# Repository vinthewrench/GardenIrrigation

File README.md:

# GardenIrrigation

This is the hardware for Farm automation made easy as Pi

The entire series is at https://www.vinthewrench.com/p/off-grid-farm-automation-raspberry-pi

Garden Irrigation Board

<object data="Garden PCB schematic.pdf" type="application/pdf" width="600px" height="500px">
    <embed src="Garden PCB schematic.pdf">
        <p>This browser does not support PDFs. Please download the PDF to view it: <a href="Garden PCB schematic.pdf">Download PDF</a>.</p>
    </embed>
</object>

DRV103 Plugin Board

<object data="DRV103 Solenoid Driver Board.pdf" type="application/pdf" width="600px" height="500px">
    <embed src="DRV103 Solenoid Driver Board.pdf">
        <p>This browser does not support PDFs. Please download the PDF to view it: <a href="DRV103 Solenoid Driver Board.pdf">Download PDF</a>.</p>
    </embed>
</object>

# Articles

* [Farm automation made easy as Pi](https://www.vinthewrench.com/p/raspberry-pi-internet-of-things-part)
* [Controlling the Irrigation valves.](https://www.vinthewrench.com/p/raspberry-pi-internet-of-things-part-23c)
* [Reading the Temperature with 1-wire Sensors](https://www.vinthewrench.com/p/raspberry-pi-internet-of-things-part-a4c)
* [Using the I2C protocol to communicate to sensors.](https://www.vinthewrench.com/p/raspberry-pi-internet-of-things-part-688)
* [Reading Environmental Data with I2C](https://www.vinthewrench.com/p/raspberry-pi-internet-of-things-part-a03)
* [Rain Sensors](https://www.vinthewrench.com/p/raspberry-pi-internet-of-things-part-cfd)
* [More I/O](https://www.vinthewrench.com/p/raspberry-pi-internet-of-things-part-61b)
* [Getting the data and controlling the devices from the REST API](https://www.vinthewrench.com/p/raspberry-pi-internet-of-things-part-8e7)
* [Writing your own device plug-ins](https://www.vinthewrench.com/p/raspberry-pi-internet-of-things-part-9ef)
* [Using software devices to build on the hardware.](https://www.vinthewrench.com/p/raspberry-pi-internet-of-things-part-094)
* [How to make things happen automatically](https://www.vinthewrench.com/p/raspberry-pi-internet-of-things-part-12f)
* [How to make things happen on time](https://www.vinthewrench.com/p/raspberry-pi-internet-of-things-part-eb8)
* [There are always conditions to evaluate](https://www.vinthewrench.com/p/raspberry-pi-internet-of-things-part-3aa)
* [Rolling my own I²C and 1-Wire interface card](https://www.vinthewrench.com/p/raspberry-pi-internet-of-things-part-2a8)

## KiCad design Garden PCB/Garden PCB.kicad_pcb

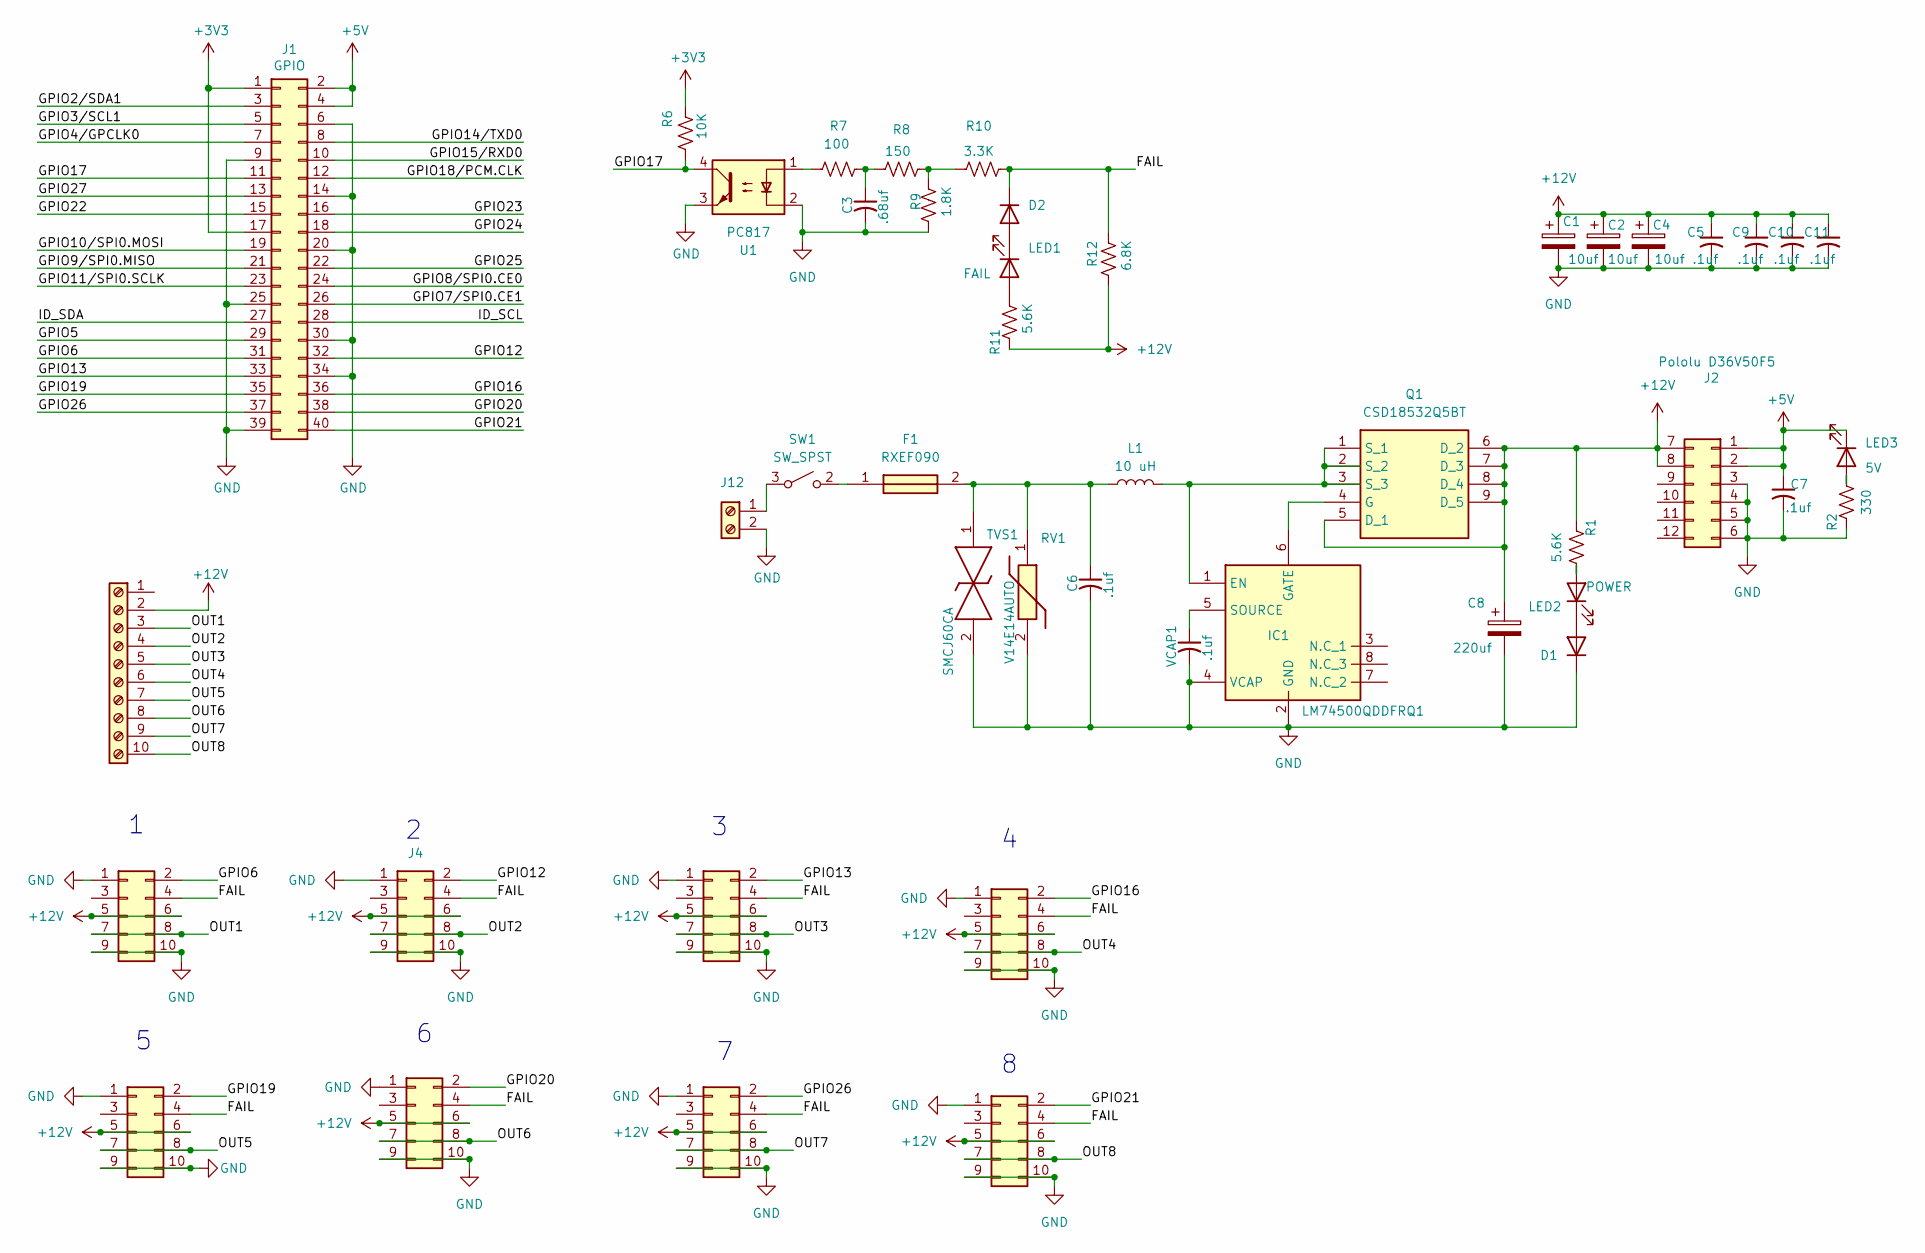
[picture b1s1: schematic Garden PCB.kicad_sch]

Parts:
C1, C2, C4: 10uf; CP_Radial_D5.0mm_P2.00mm
C3: .68uf; C_0805_2012Metric_Pad1.18x1.45mm_HandSolder
C5, C7, C9, C10, C11: .1uf; RCER71H104K0DBH03A
C6: .1uf; C_0805_2012Metric_Pad1.18x1.45mm_HandSolder
C8: 220uf; CP_Radial_D5.0mm_P2.00mm
D1, D2: 1N4148WS-7-F; D_SOD-323_HandSoldering
F1: RXEF090; RXEF0902; Manufacturer_Part_Number RXEF090-2; Mouser Part Number 650-RXEF090-2
IC1: LM74500QDDFRQ1; SOT65P280X110-8N; Mouser Part Number 595-LM74500QDDFRQ1
J1: GPIO; PinSocket_2x20_P2.54mm_Vertical
J2: Conn_02x06_Top_Bottom; PinSocket_2x06_P2.54mm_Vertical
J3, J4, J5, J6, J7, J8, J9, J10: Conn_02x05_Odd_Even; PinSocket_2x05_P2.54mm_Vertical
J11: Screw_Terminal_01x10; TerminalBlock_Phoenix_MKDS-1,5-10-5.08_1x10_P5.08mm_Horizon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
J12: Screw_Terminal_01x02; TerminalBlock_Phoenix_MKDS-1,5-2-5.08_1x02_P5.08mm_Horizont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
L1: 10 uH; L_Toroid_Vertical_L21.6mm_W9.1mm_P8.40mm_Bourns_5700
LED1: APT2012SURCK; LED_0805_2012Metric_Pad1.15x1.40mm_HandSolder
LED2, LED3: LG M67K-H1J2-24-Z; LED_0805_2012Metric_Pad1.15x1.40mm_HandSolder
Q1: CSD18532Q5BT; Manufacturer_Part_Number CSD18532Q5BT; Mouser Part Number 595-CSD18532Q5BT
R1, R11: 5.6K; R_0805_2012Metric_Pad1.20x1.40mm_HandSolder
R2: 330; R_0805_2012Metric_Pad1.20x1.40mm_HandSolder
R6: 10K; R_0805_2012Metric_Pad1.20x1.40mm_HandSolder
R7: 100; R_0805_2012Metric_Pad1.20x1.40mm_HandSolder
R8: 150; R_0805_2012Metric_Pad1.20x1.40mm_HandSolder
R9: 1.8K; R_0805_2012Metric_Pad1.20x1.40mm_HandSolder
R10: 3.3K; R_0805_2012Metric_Pad1.20x1.40mm_HandSolder
R12: 6.8K; R_0805_2012Metric_Pad1.20x1.40mm_HandSolder
RV1: V14E14AUTO; Manufacturer_Part_Number V14E14AUTO; Mouser Part Number 576-V14E14AUTO
SW1: SW_SPST; 7105SYV3QE
TVS1: SMCJ60CA; DIONM7959X262N; Manufacturer_Part_Number SMCJ60CA; Mouser Part Number 652-SMCJ60CA
U1: PC817; DIP-4_W7.62mm
VCAP1: .1uf; C_0805_2012Metric_Pad1.18x1.45mm_HandSolder

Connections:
+3V3: J1.1, J1.17, R6.2
+5V: C7.1, J1.2, J1.4, J2.1, J2.2, LED3.1 (K)
+12V: C1.1, C2.1, C4.1, C5.1, C8.1, C9.1, C10.1, C11.1, J2.7, J2.8, J3.5, J3.6, J4.5, J4.6, J5.5, J5.6, J6.5, J6.6, J7.5, J7.6, J8.5, J8.6, J9.5, J9.6, J10.5, J10.6, J11.2, Q1.5 (D_1), Q1.6 (D_2), Q1.7 (D_3), Q1.8 (D_4), Q1.9 (D_5), R1.1, R11.1, R12.1
/FAIL: D2.1 (K), J3.4, J4.4, J5.4, J6.4, J7.4, J8.4, J9.4, J10.4, R10.2, R12.2
/GPIO2/SDA1: J1.3
/GPIO3/SCL1: J1.5
/GPIO4/GPCLK0: J1.7
/GPIO5: J1.29
/GPIO6: J1.31, J3.2
/GPIO7/SPI0.CE1: J1.26
/GPIO8/SPI0.CE0: J1.24
/GPIO9/SPI0.MISO: J1.21
/GPIO10/SPI0.MOSI: J1.19
/GPIO11/SPI0.SCLK: J1.23
/GPIO12: J1.32, J4.2
/GPIO13: J1.33, J6.2
/GPIO14/TXD0: J1.8
/GPIO15/RXD0: J1.10
/GPIO16: J1.36, J5.2
/GPIO17: J1.11, R6.1, U1.4
/GPIO18/PCM.CLK: J1.12
/GPIO19: J1.35, J8.2
/GPIO20: J1.38, J7.2
/GPIO21: J1.40, J9.2
/GPIO22: J1.15
/GPIO23: J1.16
/GPIO24: J1.18
/GPIO25: J1.22
/GPIO26: J1.37, J10.2
/GPIO27: J1.13
/ID_SCL: J1.28
/ID_SDA: J1.27
/OUT1: J3.7, J3.8, J11.3
/OUT2: J4.7, J4.8, J11.4
/OUT3: J6.7, J6.8, J11.5
/OUT4: J5.7, J5.8, J11.6
/OUT5: J8.7, J8.8, J11.7
/OUT6: J7.7, J7.8, J11.8
/OUT7: J10.7, J10.8, J11.9
/OUT8: J9.7, J9.8, J11.10
GND: C1.2, C2.2, C3.2, C4.2, C5.2, C6.2, C7.2, C8.2, C9.2, C10.2, C11.2, D1.1 (K), IC1.2 (GND), IC1.4 (VCAP), J1.6, J1.9, J1.14, J1.20, J1.25, J1.30, J1.34, J1.39, J2.3, J2.4, J2.5, J2.6, J3.1, J3.9, J3.10, J4.1, J4.9, J4.10, J5.1, J5.9, J5.10, J6.1, J6.9, J6.10, J7.1, J7.9, J7.10, J8.1, J8.9, J8.10, J9.1, J9.9, J9.10, J10.1, J10.9, J10.10, J12.2, R2.1, R9.2, RV1.2, TVS1.2, U1.2, U1.3, VCAP1.2
unnamed: C3.1, R7.2, R8.1
unnamed: C6.1, F1.2, L1.1, RV1.1, TVS1.1
unnamed: D1.2 (A), LED2.1 (K)
unnamed: D2.2 (A), LED1.1 (K)
unnamed: IC1.1 (EN), L1.2, Q1.1 (S_1), Q1.2 (S_2), Q1.3 (S_3)
unnamed: IC1.6 (GATE), Q1.4 (G)
unnamed: IC1.5 (SOURCE), VCAP1.1
unnamed: J12.1, SW1.3 (A)
unnamed: LED1.2 (A), R11.2
unnamed: LED2.2 (A), R1.2
unnamed: LED3.2 (A), R2.2
unnamed: R7.1, U1.1
unnamed: R8.2, R9.1, R10.1
unnamed: F1.1, SW1.2 (B)

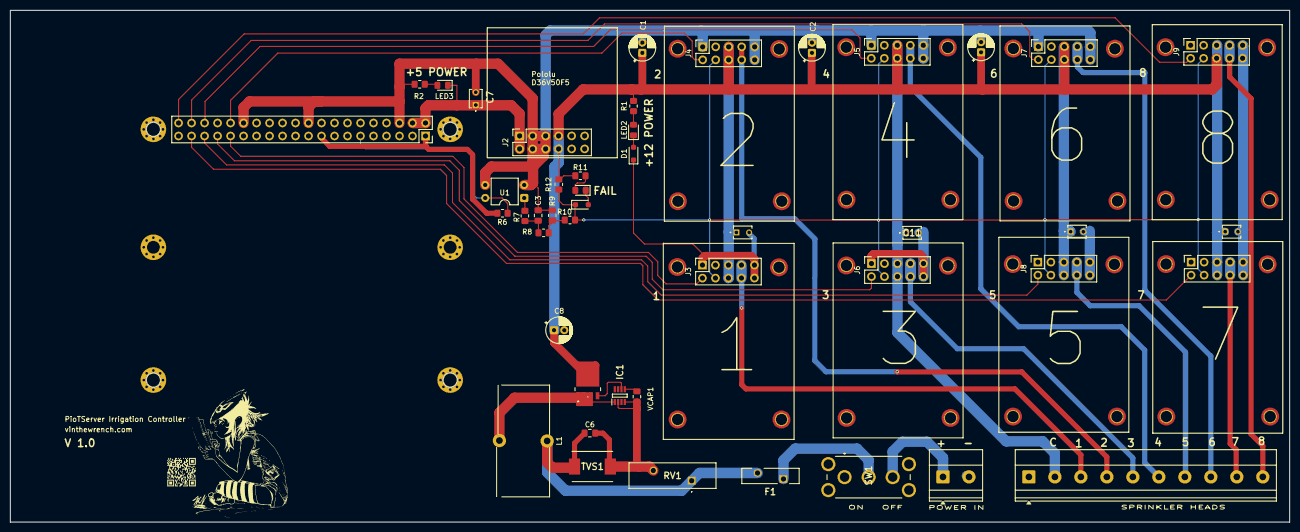
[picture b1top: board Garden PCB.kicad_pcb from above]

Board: 2 copper layers, 250.0 x 100.0 mm, 53 parts (1 on the bottom side), 36 nets.

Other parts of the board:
MH1, MH2, MH3, MH4, MH5, MH6: MountingHole_2.5mm_Pad_Via
RP?: Raspberry_Pi_2_3; raspberrypi_2_3

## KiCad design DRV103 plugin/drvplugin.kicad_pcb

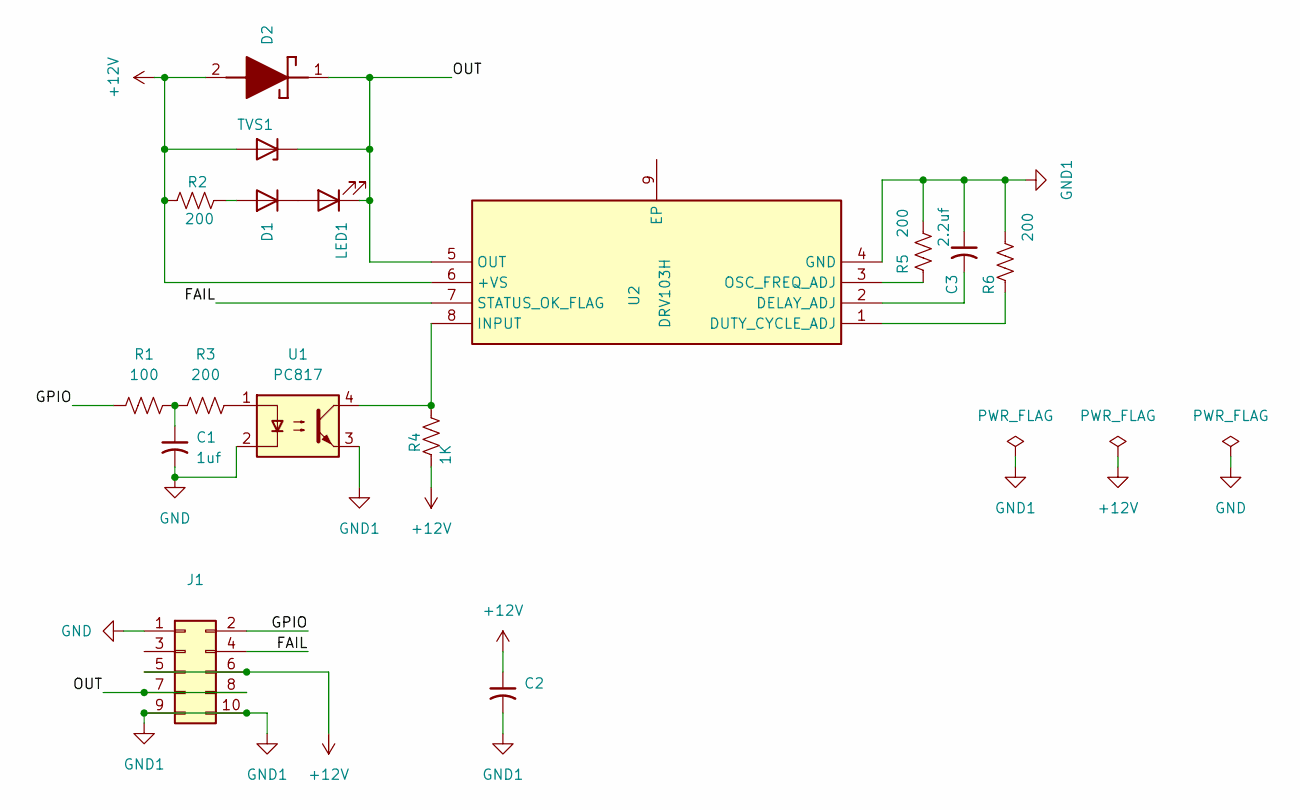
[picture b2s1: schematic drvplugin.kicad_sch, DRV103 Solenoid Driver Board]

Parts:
C1: 1uf; C_0805_2012Metric_Pad1.18x1.45mm_HandSolder
C2: .1uf; C_0805_2012Metric_Pad1.18x1.45mm_HandSolder
C3: 2.2uf; C_0805_2012Metric_Pad1.18x1.45mm_HandSolder
D1: 1N4148; D_SOD-323_HandSoldering
D2: VS-30BQ040; DIOM7959X262N; Mouser Part Number 583-SR340-T
J1: Conn_02x05_Odd_Even; PinHeader_2x05_P2.54mm_Vertical
LED1: LG M67K-H1J2-24-Z; LED_0805_2012Metric_Pad1.15x1.40mm_HandSolder
R1: 100; R_0805_2012Metric_Pad1.20x1.40mm_HandSolder
R2, R3, R5, R6: 200; R_0805_2012Metric_Pad1.20x1.40mm_HandSolder
R4: 1K; R_0805_2012Metric_Pad1.20x1.40mm_HandSolder
TVS1: P6SMB18A; D_SMB_Handsoldering
U1: PC817; DIP-4_W7.62mm
U2: DRV103H; SOIC127P600X170-9N; Mouser Part Number 595-DRV103H

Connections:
+12V: C2.1, D2.2 (A), J1.5, J1.6, R2.1, R4.1, TVS1.2 (A), U2.6 (+VS)
/FAIL: J1.4, U2.7 (STATUS_OK_FLAG)
/GPIO: J1.2, R1.2
/OUT: D2.1 (K), J1.7, J1.8, LED1.1 (K), TVS1.1 (K), U2.5 (OUT)
GND: C1.2, J1.1, U1.2
GND1: C2.2, C3.1, J1.9, J1.10, R5.2, R6.2, U1.3, U2.4 (GND)
unnamed: C1.1, R1.1, R3.2
unnamed: D1.2 (A), R2.2
unnamed: D1.1 (K), LED1.2 (A)
unnamed: R3.1, U1.1
unnamed: C3.2, U2.2 (DELAY_ADJ)
unnamed: R6.1, U2.1 (DUTY_CYCLE_ADJ)
unnamed: R4.2, U1.4, U2.8 (INPUT)
unnamed: R5.1, U2.3 (OSC_FREQ_ADJ)

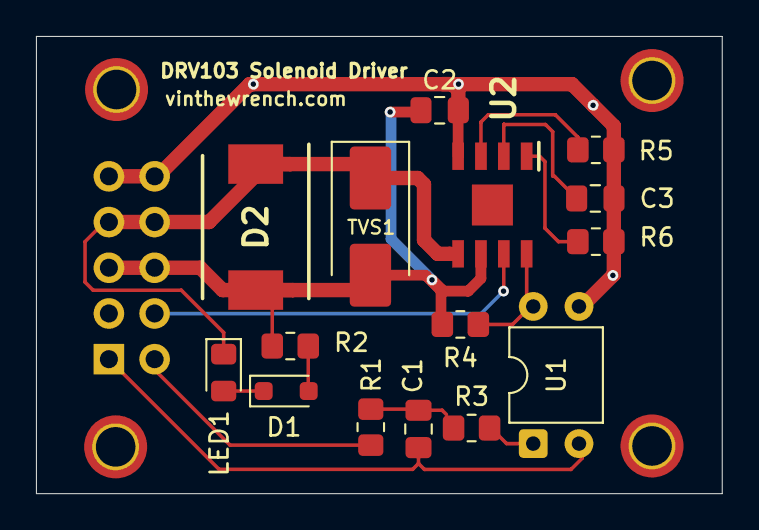
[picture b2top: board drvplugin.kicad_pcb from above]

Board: 2 copper layers, 38.1 x 25.4 mm, 16 parts (1 on the bottom side), 14 nets.

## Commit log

2025-07-17 added PDFs and PNG
2025-07-17 better readme
2025-07-17 no message
2025-07-22 fixes for power switch, also looks like KiCad might have boned some of our pinouts
